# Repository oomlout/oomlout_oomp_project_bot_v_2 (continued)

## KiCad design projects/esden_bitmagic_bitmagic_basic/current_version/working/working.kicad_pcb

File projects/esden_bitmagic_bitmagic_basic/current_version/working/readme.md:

# bitmagic
 
## summary 
* id: esden_bitmagic_bitmagic_basic
* user: esden
* name: bitmagic
* board: bitmagic_basic
* repo: https://github.com/esden/bitmagic
* src_file_repo_kicad_pcb: bmb/v1.1a/bitmagic-basic.kicad_pcb
* src_file_repo_kicad_pcb_link: https://github.com/esden/bitmagic/tree/master/bmb/v1.1a/bitmagic-basic.kicad_pcb
* src_file_repo_kicad_sch: bmb/v1.1a/bitmagic-basic.kicad_sch
* src_file_repo_kicad_sch_link: https://github.com/esden/bitmagic/tree/master/bmb/v1.1a/bitmagic-basic.kicad_sch

* src_file_repo_sch: bmb/v1.0b/bitmagic-basic.sch
* src_file_repo_sch_link: https://github.com/esden/bitmagic/tree/master/bmb/v1.0b/bitmagic-basic.sch
* full details link: https://github.com/oomlout/oomlout_oomp_project_bot_v_2/tree/main/projects/esden_bitmagic_bitmagic_basic/current_version/working

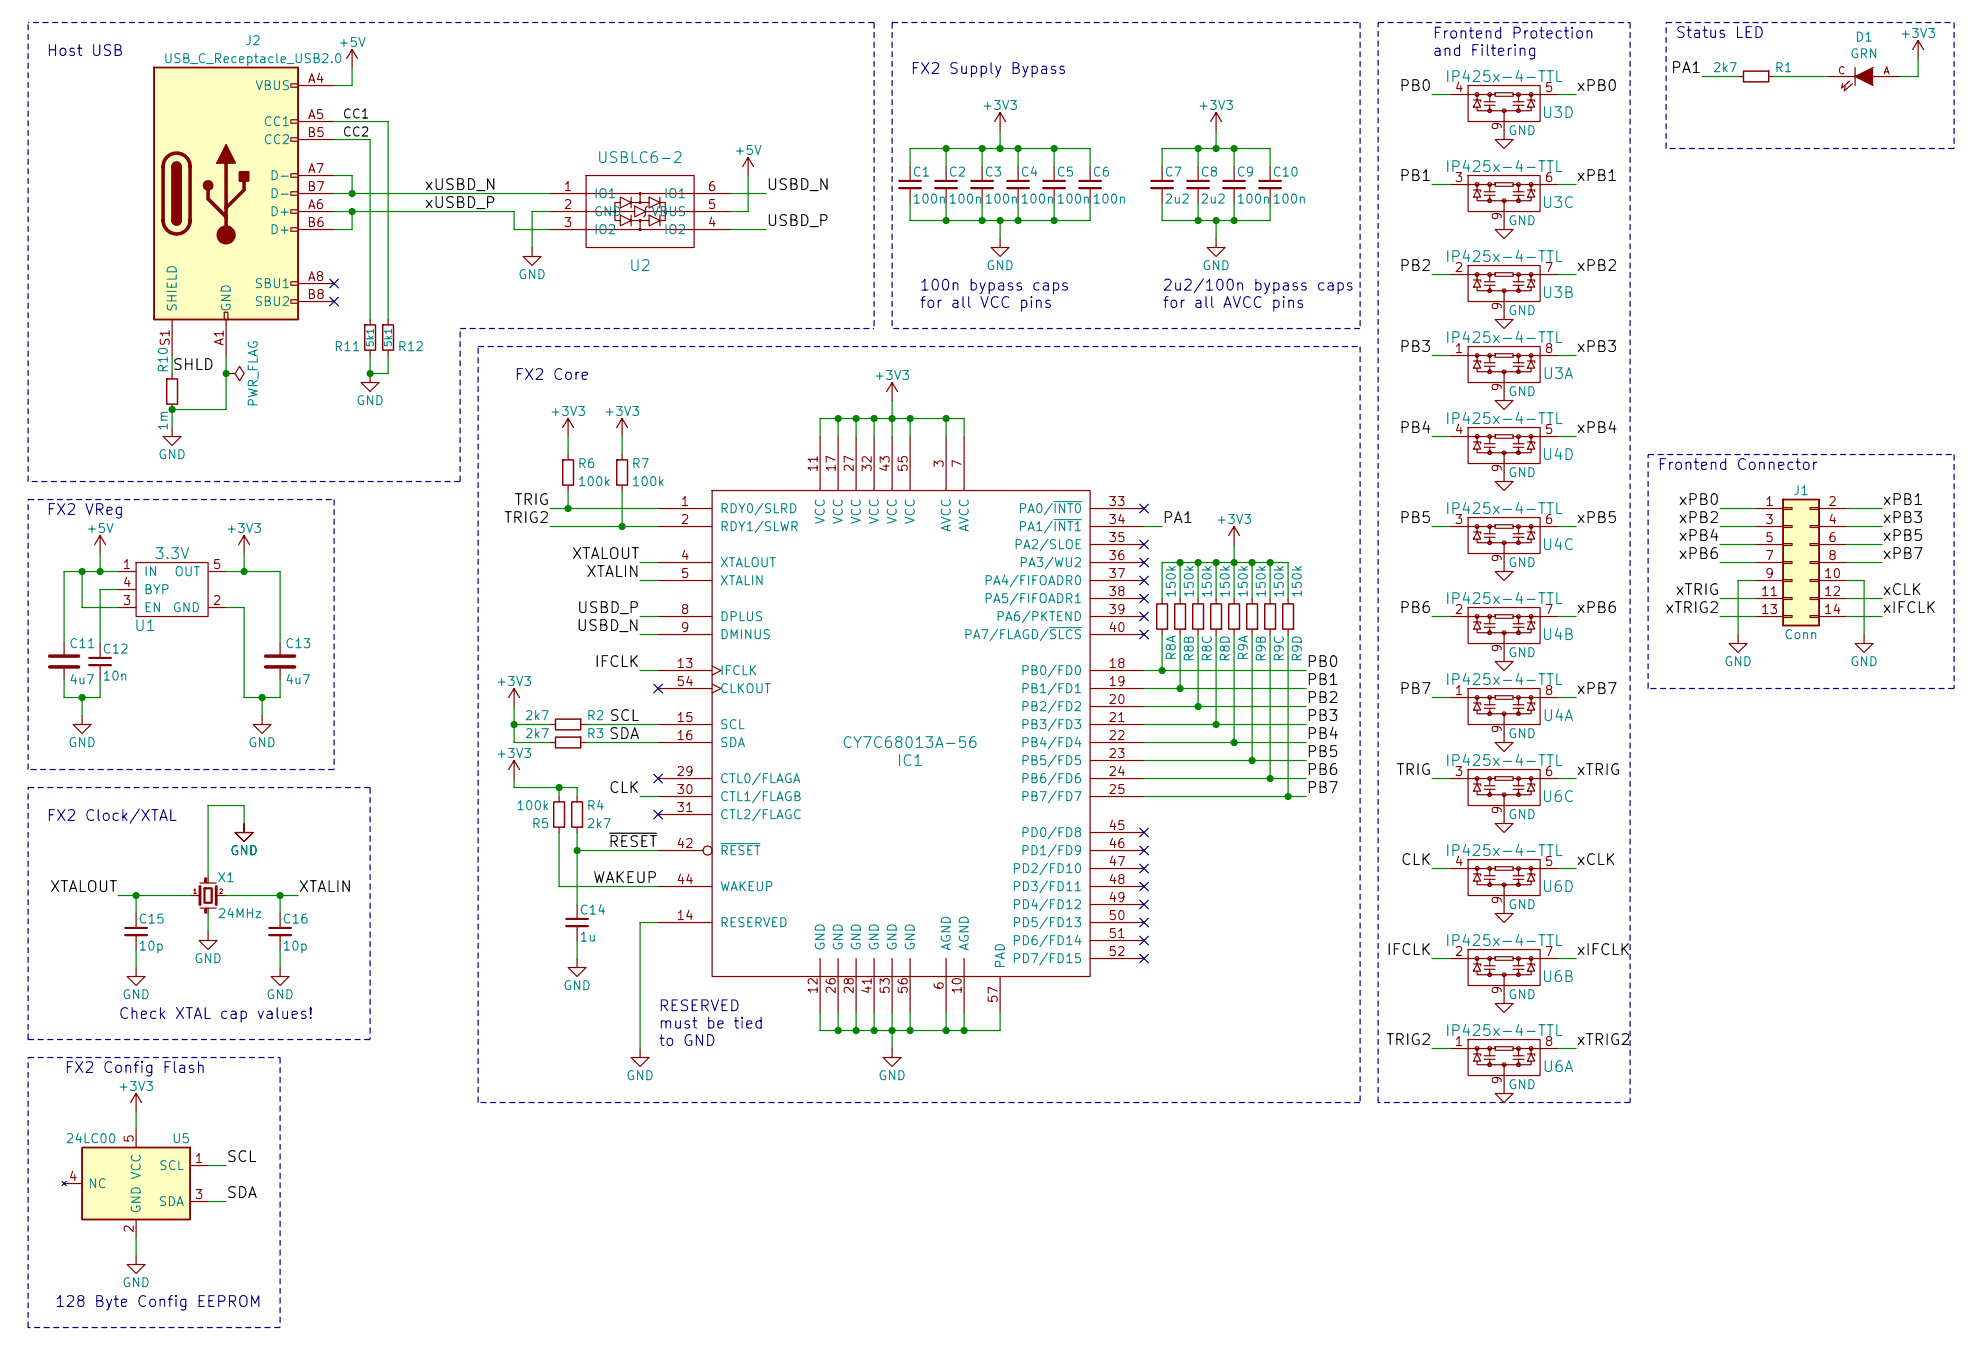
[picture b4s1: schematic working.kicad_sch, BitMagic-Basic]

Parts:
C1, C2, C3, C4, C5, C6, C9, C10: 100n; C_0402
C7, C8: 2u2; C_0402
C11, C13: 4u7; C_0603
C12: 10n; C_0402
C14: 1u; C_0402
C15, C16: 10p; C_0402
D1: GRN; D_0603
IC1: CY7C68013A-56; QFN-56-1EP_8x8mm_Pitch0.5mm
J1: Conn; PinHeader_2x07_P1.27mm_Vertical_SMD
J2: USB_C_Receptacle_USB2.0; USB_C_Receptacle_HRO_TYPE-C-31-M-12
R1, R2, R3, R4: 2k7; R_0402
R5, R6, R7: 100k; R_0402
R8, R9: 150k; R_Array_Convex_4x0402
R10: 1m; R_0402
R11, R12: 5k1; R_0402
U1: 3.3V; SOT-23-5
U2: USBLC6-2; SOT-666
U3, U4, U6: IP425x-4-TTL; DFN-8-1EP_1.35x1.7mm_Pitch0.4mm
U5: 24LC00; SOT-23-5
X1: 24MHz; ABM8

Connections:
+3V3: C1.1, C2.1, C3.1, C4.1, C5.1, C6.1, C7.1, C8.1, C9.1, C10.1, C13.1, D1.A, IC1.3 (AVCC), IC1.7 (AVCC), IC1.11 (VCC), IC1.17 (VCC), IC1.27 (VCC), IC1.32 (VCC), IC1.43 (VCC), IC1.55 (VCC), R2.2, R3.2, R4.2, R5.2, R6.1, R7.1, R8.2, R8.4, R8.6, R8.8, R9.2, R9.4, R9.6, R9.8, U1.5 (OUT), U5.5 (VCC)
+5V: C11.1, J2.A4 (VBUS), J2.A9 (VBUS), J2.B4 (VBUS), J2.B9 (VBUS), U1.1 (IN), U1.3 (EN), U2.5 (VBUS)
/CC1: J2.A5 (CC1), R12.1
/CC2: J2.B5 (CC2), R11.1
/CLK: IC1.30 (CTL1/FLAGB), U6.4
/IFCLK: IC1.13 (IFCLK), U6.2
/PA1: IC1.34 (PA1/~INT1), R1.2
/PB0: IC1.18 (PB0/FD0), R8.1, U3.4
/PB1: IC1.19 (PB1/FD1), R8.3, U3.3
/PB2: IC1.20 (PB2/FD2), R8.5, U3.2
/PB3: IC1.21 (PB3/FD3), R8.7, U3.1
/PB4: IC1.22 (PB4/FD4), R9.1, U4.4
/PB5: IC1.23 (PB5/FD5), R9.3, U4.3
/PB6: IC1.24 (PB6/FD6), R9.5, U4.2
/PB7: IC1.25 (PB7/FD7), R9.7, U4.1
/SCL: IC1.15 (SCL), R2.1, U5.1 (SCL)
/SDA: IC1.16 (SDA), R3.1, U5.3 (SDA)
/SHLD: J2.S1 (SHIELD), R10.1
/TRIG: IC1.1 (RDY0/SLRD), R6.2, U6.3
/TRIG2: IC1.2 (RDY1/SLWR), R7.2, U6.1
/USBD_N: IC1.9 (DMINUS), U2.6 (IO1)
/USBD_P: IC1.8 (DPLUS), U2.4 (IO2)
/WAKEUP: IC1.44 (WAKEUP), R5.1
/XTALIN: C16.1, IC1.5 (XTALIN), X1.2
/XTALOUT: C15.1, IC1.4 (XTALOUT), X1.1
/xCLK: J1.12, U6.5
/xIFCLK: J1.14, U6.7
/xPB0: J1.1, U3.5
/xPB1: J1.2, U3.6
/xPB2: J1.3, U3.7
/xPB3: J1.4, U3.8
/xPB4: J1.5, U4.5
/xPB5: J1.6, U4.6
/xPB6: J1.7, U4.7
/xPB7: J1.8, U4.8
/xTRIG: J1.11, U6.6
/xTRIG2: J1.13, U6.8
/xUSBD_N: J2.A7 (D-), J2.B7 (D-), U2.1 (IO1)
/xUSBD_P: J2.A6 (D+), J2.B6 (D+), U2.3 (IO2)
/~RESET: C14.1, IC1.42 (~RESET), R4.1
GND: C1.2, C2.2, C3.2, C4.2, C5.2, C6.2, C7.2, C8.2, C9.2, C10.2, C11.2, C12.2, C13.2, C14.2, C15.2, C16.2, IC1.6 (AGND), IC1.10 (AGND), IC1.12 (GND), IC1.14 (RESERVED), IC1.26 (GND), IC1.28 (GND), IC1.41 (GND), IC1.53 (GND), IC1.56 (GND), IC1.57 (PAD), J1.9, J1.10, J2.A1 (GND), J2.A12 (GND), J2.B1 (GND), J2.B12 (GND), R10.2, R11.2, R12.2, U1.2 (GND), U2.2 (GND), U3.9, U4.9, U5.2 (GND), U6.9, X1.GND (case)
unnamed: C12.1, U1.4 (BYP)
unnamed: D1.C, R1.1
no_connect_44: IC1.29 (CTL0/FLAGA)
no_connect_45: IC1.31 (CTL2/FLAGC)
no_connect_46: IC1.33 (PA0/~INT0)
no_connect_47: IC1.35 (PA2/SLOE)
no_connect_48: IC1.36 (PA3/WU2)
no_connect_49: IC1.37 (PA4/FIFOADR0)
no_connect_50: IC1.38 (PA5/FIFOADR1)
no_connect_51: IC1.39 (PA6/PKTEND)
no_connect_52: IC1.40 (PA7/FLAGD/~SLCS)
no_connect_53: IC1.45 (PD0/FD8)
no_connect_54: IC1.46 (PD1/FD9)
no_connect_55: IC1.47 (PD2/FD10)
no_connect_56: IC1.48 (PD3/FD11)
no_connect_57: IC1.49 (PD4/FD12)
no_connect_58: IC1.50 (PD5/FD13)
no_connect_59: IC1.51 (PD6/FD14)
no_connect_60: IC1.52 (PD7/FD15)
no_connect_61: IC1.54 (CLKOUT)
no_connect_62: J2.A8 (SBU1)
no_connect_63: J2.B8 (SBU2)
no_connect_64: U5.4 (NC)

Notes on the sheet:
100n bypass caps for all VCC pins
FX2 Core
Check XTAL cap values!
Host USB
RESERVED must be tied to GND
FX2 Clock/XTAL
Status LED
Frontend Connector
128 Byte Config EEPROM
2u2/100n bypass caps for all AVCC pins
Frontend Protection and Filtering
FX2 VReg
FX2 Supply Bypass
FX2 Config Flash

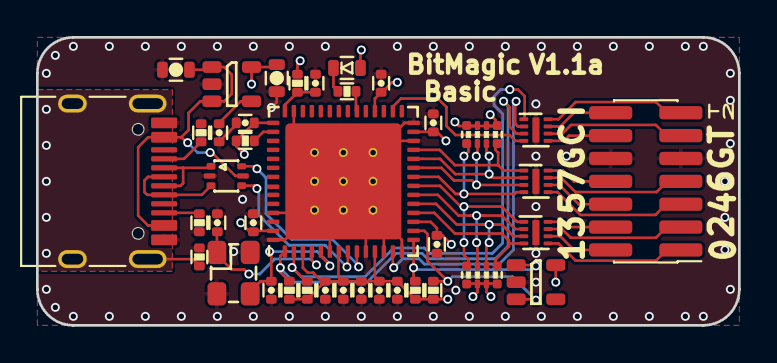
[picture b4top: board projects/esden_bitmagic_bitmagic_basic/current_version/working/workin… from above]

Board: 4 copper layers, 39.0 x 16.0 mm, 39 parts (0 on the bottom side), 43 nets.

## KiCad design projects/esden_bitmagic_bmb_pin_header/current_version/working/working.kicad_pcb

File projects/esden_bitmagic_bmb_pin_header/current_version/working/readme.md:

# bitmagic
 
## summary 
* id: esden_bitmagic_bmb_pin_header
* user: esden
* name: bitmagic
* board: bmb_pin_header
* repo: https://github.com/esden/bitmagic
* src_file_repo_kicad_pcb: adapters/bmb-pin-header-v1_0a/bmb-pin-header.kicad_pcb
* src_file_repo_kicad_pcb_link: https://github.com/esden/bitmagic/tree/master/adapters/bmb-pin-header-v1_0a/bmb-pin-header.kicad_pcb

* src_file_repo_sch: adapters/bmb-pin-header-v1_0a/bmb-pin-header.sch
* src_file_repo_sch_link: https://github.com/esden/bitmagic/tree/master/adapters/bmb-pin-header-v1_0a/bmb-pin-header.sch
* full details link: https://github.com/oomlout/oomlout_oomp_project_bot_v_2/tree/main/projects/esden_bitmagic_bmb_pin_header/current_version/working

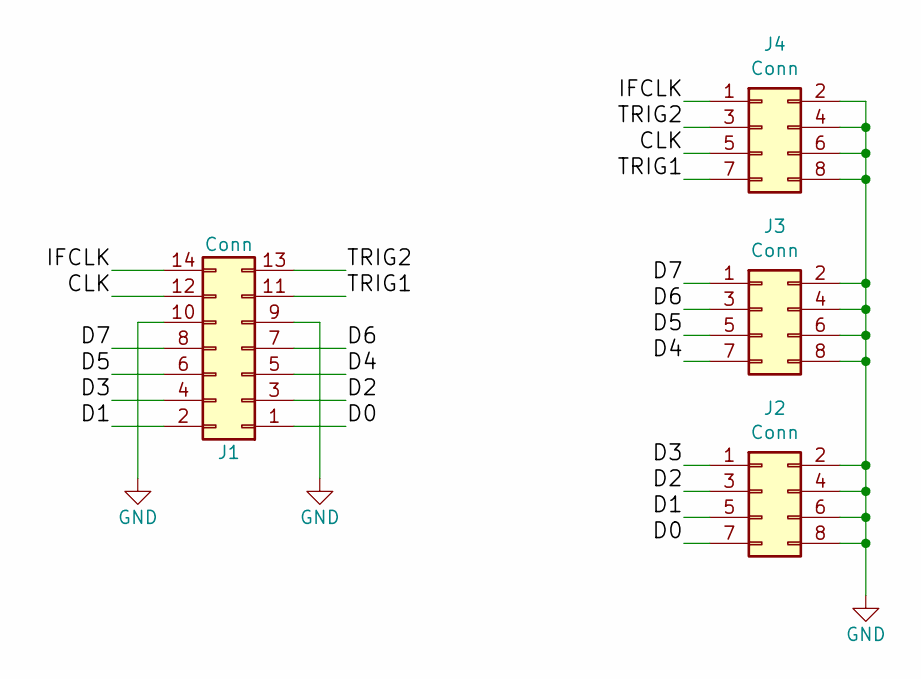
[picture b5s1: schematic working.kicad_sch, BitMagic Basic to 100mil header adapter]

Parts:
J1: Conn; PinHeader_2x07_P1.27mm_Vertical_SMD
J2, J3, J4: Conn; PinHeader_2x04_P2.54mm_Horizontal

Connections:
/CLK: J1.12, J4.5
/D0: J1.1, J2.7
/D1: J1.2, J2.5
/D2: J1.3, J2.3
/D3: J1.4, J2.1
/D4: J1.5, J3.7
/D5: J1.6, J3.5
/D6: J1.7, J3.3
/D7: J1.8, J3.1
/IFCLK: J1.14, J4.1
/TRIG1: J1.11, J4.7
/TRIG2: J1.13, J4.3
GND: J1.9, J1.10, J2.2, J2.4, J2.6, J2.8, J3.2, J3.4, J3.6, J3.8, J4.2, J4.4, J4.6, J4.8

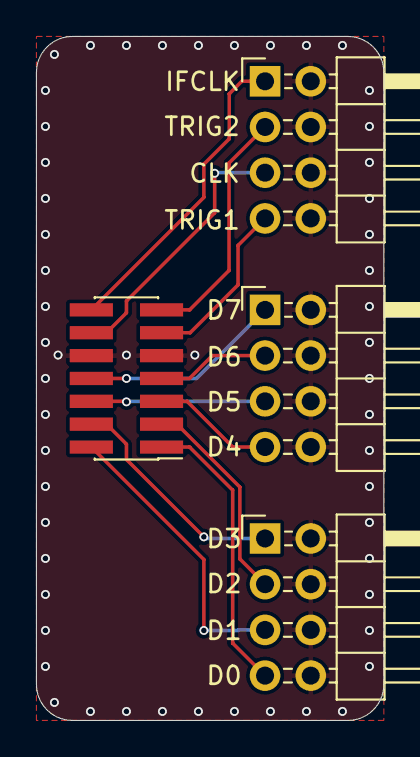
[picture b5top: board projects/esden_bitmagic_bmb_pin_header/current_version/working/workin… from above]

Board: 2 copper layers, 19.3 x 38.0 mm, 4 parts (0 on the bottom side), 13 nets.

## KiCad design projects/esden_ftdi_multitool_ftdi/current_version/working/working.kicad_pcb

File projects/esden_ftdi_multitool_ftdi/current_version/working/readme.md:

# ftdi_multitool
 
## summary 
* id: esden_ftdi_multitool_ftdi
* user: esden
* name: ftdi_multitool
* board: ftdi
* repo: https://github.com/esden/ftdi-multitool
* src_file_repo_kicad_pcb: core/v1.0a/ftdi.kicad_pcb
* src_file_repo_kicad_pcb_link: https://github.com/esden/ftdi-multitool/tree/master/core/v1.0a/ftdi.kicad_pcb

* src_file_repo_sch: core/v1.0a/ftdi.sch
* src_file_repo_sch_link: https://github.com/esden/ftdi-multitool/tree/master/core/v1.0a/ftdi.sch
* full details link: https://github.com/oomlout/oomlout_oomp_project_bot_v_2/tree/main/projects/esden_ftdi_multitool_ftdi/current_version/working

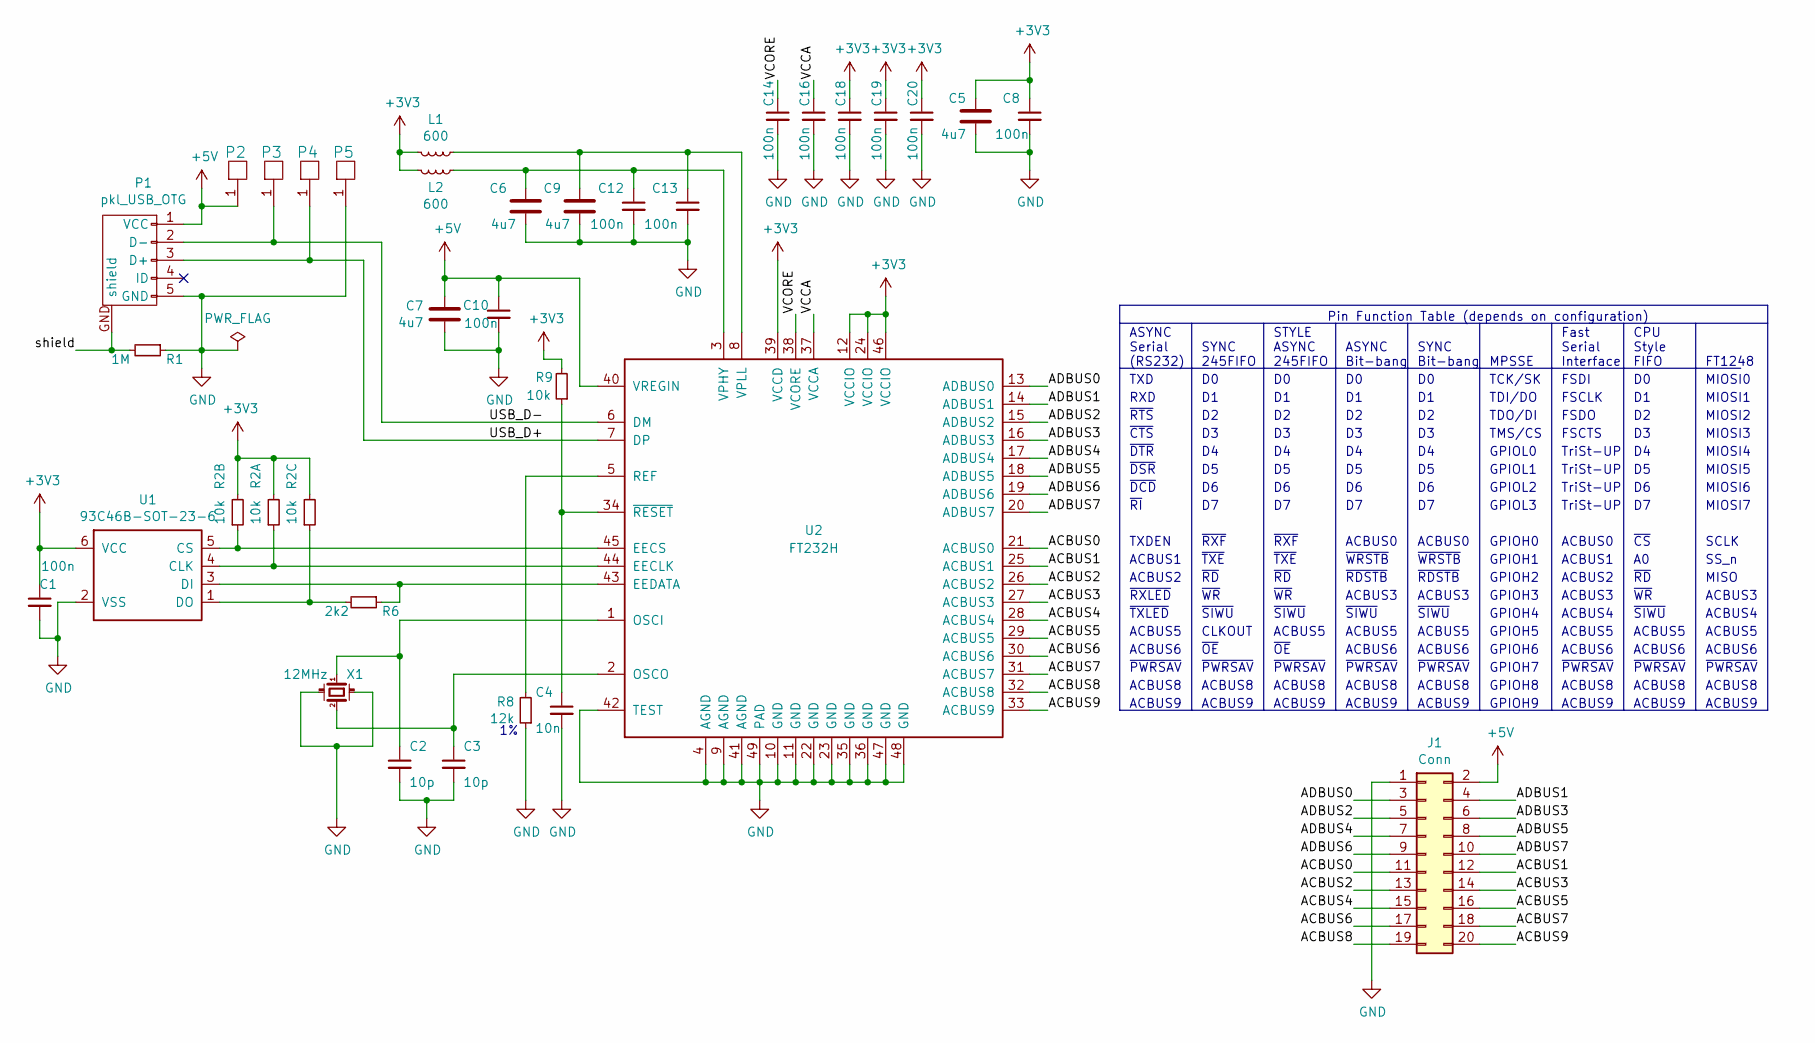
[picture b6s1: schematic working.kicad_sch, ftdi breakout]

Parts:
C1, C8, C10, C12, C13, C14, C16, C18, C19, C20: 100n; C_0402
C2, C3: 10p; C_0402
C4: 10n; C_0402
C5, C6, C7, C9: 4u7; C_0603
J1: Conn; FTSH-EDGE-20pin
L1, L2: 600; L_0402
P1: pkl_USB_OTG; Connector_USB_Micro_B_SMD
P2, P3, P4, P5: UP; PAD_SMD_1x2.65
R1: 1M; R_0402
R2: 10k; R_Array_Convex_4x0402
R6: 2k2; R_0402
R8: 12k; R_0402
R9: 10k; R_0402
U1: 93C46B-SOT-23-6; SOT-23-6
U2: FT232H; QFN-48-1EP_8x8mm_Pitch0.5mm
X1: 12MHz; ABM8

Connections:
+3V3: C1.1, C5.1, C8.1, C18.1, C19.1, C20.1, L1.1, L2.1, R2.2, R2.4, R2.6, R9.2, U1.6 (VCC), U2.12 (VCCIO), U2.24 (VCCIO), U2.39 (VCCD), U2.46 (VCCIO)
+5V: C7.1, C10.1, J1.2, P1.1 (VCC), P2.1, U2.40 (VREGIN)
/ACBUS0: J1.11, U2.21 (ACBUS0)
/ACBUS1: J1.12, U2.25 (ACBUS1)
/ACBUS2: J1.13, U2.26 (ACBUS2)
/ACBUS3: J1.14, U2.27 (ACBUS3)
/ACBUS4: J1.15, U2.28 (ACBUS4)
/ACBUS5: J1.16, U2.29 (ACBUS5)
/ACBUS6: J1.17, U2.30 (ACBUS6)
/ACBUS7: J1.18, U2.31 (ACBUS7)
/ACBUS8: J1.19, U2.32 (ACBUS8)
/ACBUS9: J1.20, U2.33 (ACBUS9)
/ADBUS0: J1.3, U2.13 (ADBUS0)
/ADBUS1: J1.4, U2.14 (ADBUS1)
/ADBUS2: J1.5, U2.15 (ADBUS2)
/ADBUS3: J1.6, U2.16 (ADBUS3)
/ADBUS4: J1.7, U2.17 (ADBUS4)
/ADBUS5: J1.8, U2.18 (ADBUS5)
/ADBUS6: J1.9, U2.19 (ADBUS6)
/ADBUS7: J1.10, U2.20 (ADBUS7)
/USB_D+: P1.3 (D+), P4.1, U2.7 (DP)
/USB_D-: P1.2 (D-), P3.1, U2.6 (DM)
/VCCA: C16.1, U2.37 (VCCA)
/VCORE: C14.1, U2.38 (VCORE)
/shield: P1.GND (shield), R1.2
GND: C1.2, C2.2, C3.2, C4.2, C5.2, C6.2, C7.2, C8.2, C9.2, C10.2, C12.2, C13.2, C14.2, C16.2, C18.2, C19.2, C20.2, J1.1, P1.5 (GND), P5.1, R1.1, R8.1, U1.2 (VSS), U2.4 (AGND), U2.9 (AGND), U2.10 (GND), U2.11 (GND), U2.22 (GND), U2.23 (GND), U2.35 (GND), U2.36 (GND), U2.41 (AGND), U2.42 (TEST), U2.47 (GND), U2.48 (GND), U2.49 (PAD), X1.GND (case)
unnamed: C2.1, U2.1 (OSCI), X1.1
unnamed: C3.1, U2.2 (OSCO), X1.2
unnamed: C4.1, R9.1, U2.34 (~RESET)
unnamed: C6.1, C12.1, L2.2, U2.3 (VPHY)
unnamed: C9.1, C13.1, L1.2, U2.8 (VPLL)
unnamed: R2.1, U1.4 (CLK), U2.44 (EECLK)
unnamed: R2.3, U1.5 (CS), U2.45 (EECS)
unnamed: R2.5, R6.2, U1.1 (DO)
unnamed: R6.1, U1.3 (DI), U2.43 (EEDATA)
unnamed: R8.2, U2.5 (REF)

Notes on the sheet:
ACBUS0
SYNC 245FIFO
CLKOUT
ACBUS9
~{OE}
ACBUS5
TriSt-UP
~{SIWU}
FSCTS
MIOSI3
~{RDSTB}
ACBUS6
~{RXLED}
ACBUS3
Fast Serial Interface
FT1248
~{WR}
ACBUS8
FSCLK
~{TXE}
~{PWRSAV}
FSDO
~{RD}
~{DTR}
SCLK
TMS/CS
ACBUS1
SS_n
MPSSE
TDO/DI
MIOSI4
~{RXF}
Pin Function Table (depends on configuration)
~{WRSTB}
MIOSI1
TXDEN
GPIOH9
MISO
SYNC Bit-bang
GPIOH5

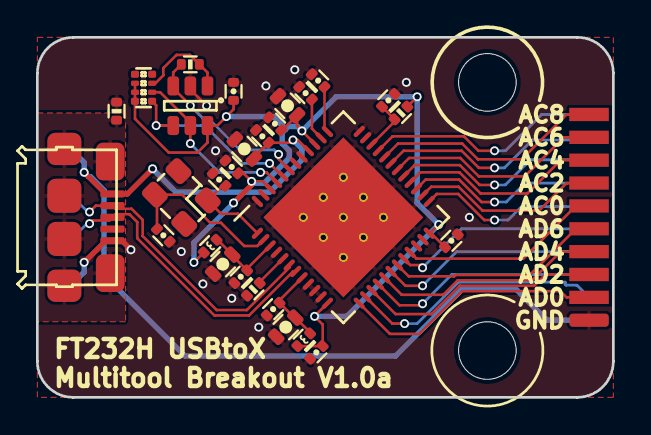
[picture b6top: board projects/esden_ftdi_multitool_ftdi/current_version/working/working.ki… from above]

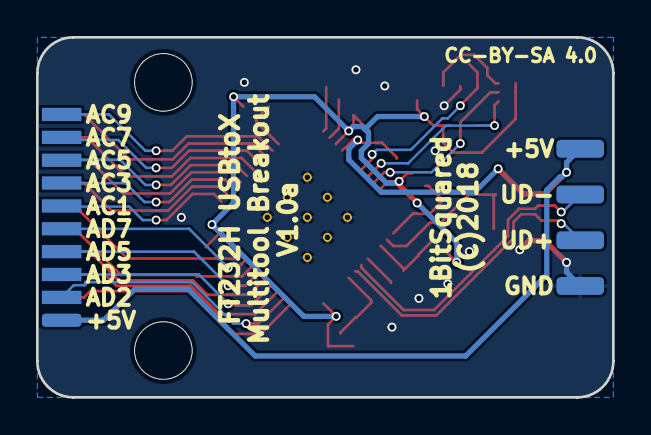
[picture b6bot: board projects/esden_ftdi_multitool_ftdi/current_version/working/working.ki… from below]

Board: 2 copper layers, 32.0 x 20.0 mm, 33 parts (4 on the bottom side), 35 nets.
